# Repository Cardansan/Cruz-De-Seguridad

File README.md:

# Cruz-De-Seguridad
Display Industria 4.0

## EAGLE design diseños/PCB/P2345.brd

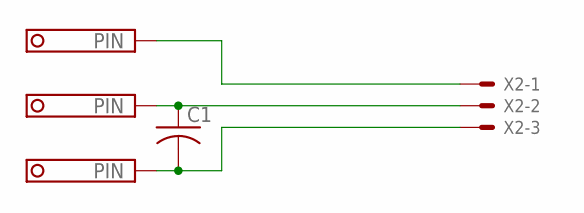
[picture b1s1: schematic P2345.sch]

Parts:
C1: C-US050-024X044; C050-024X044
X1: TERMINAL-BLOCK-3.5MM-3-PIN-ROUND-PAD; TERMINAL-BLOCK-3-PIN-3.5MM-ROUND-PAD
X2: JST-XH-03-PIN-ROUND-PAD; JST-XH-03-PACKAGE-ROUND-PAD

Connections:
unnamed: X1.1, X2.1
unnamed: C1.1, X1.2, X2.2
unnamed: C1.2, X1.3, X2.3

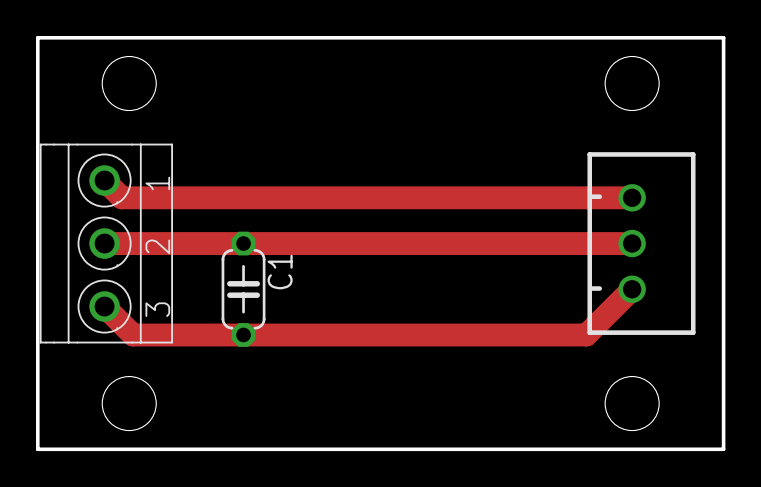
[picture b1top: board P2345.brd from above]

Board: 2 copper layers, 38.1 x 22.9 mm, 3 parts (0 on the bottom side), 3 nets.

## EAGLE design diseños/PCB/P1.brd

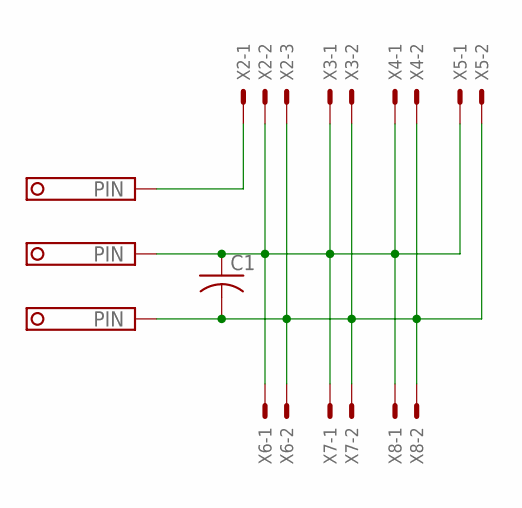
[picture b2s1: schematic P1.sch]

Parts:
C1: C-US050-024X044; C050-024X044
X1: TERMINAL-BLOCK-3.5MM-3-PIN-ROUND-PAD; TERMINAL-BLOCK-3-PIN-3.5MM-ROUND-PAD
X2: JST-XH-03-PIN-ROUND-PAD; JST-XH-03-PACKAGE-ROUND-PAD
X3, X4, X5, X6, X7, X8: JST-XH-02-PIN-ROUND-PAD; JST-XH-02-PACKAGE-ROUND-PAD

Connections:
unnamed: X1.1, X2.1
unnamed: C1.2, X1.3, X2.3, X3.2, X4.2, X5.2, X6.2, X7.2, X8.2
unnamed: C1.1, X1.2, X2.2, X3.1, X4.1, X5.1, X6.1, X7.1, X8.1

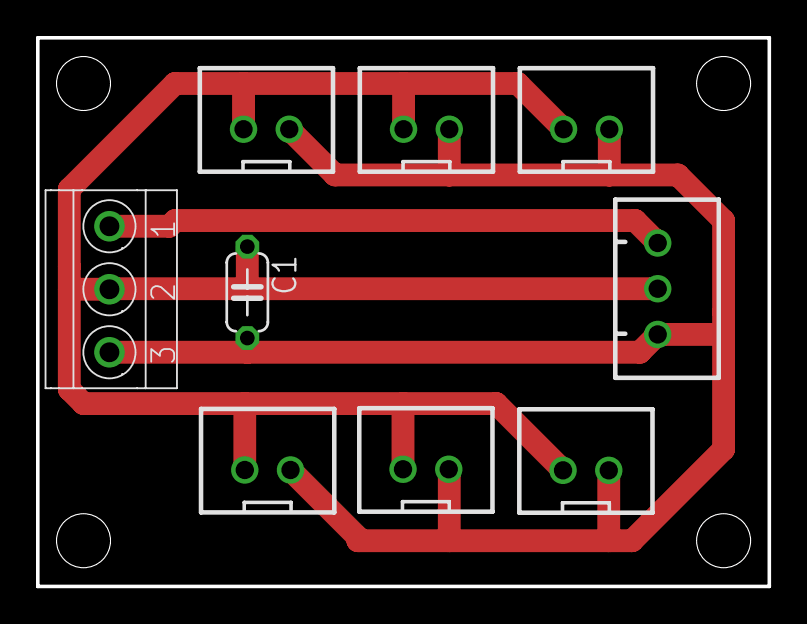
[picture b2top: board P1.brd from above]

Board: 2 copper layers, 40.6 x 30.5 mm, 9 parts (0 on the bottom side), 3 nets.

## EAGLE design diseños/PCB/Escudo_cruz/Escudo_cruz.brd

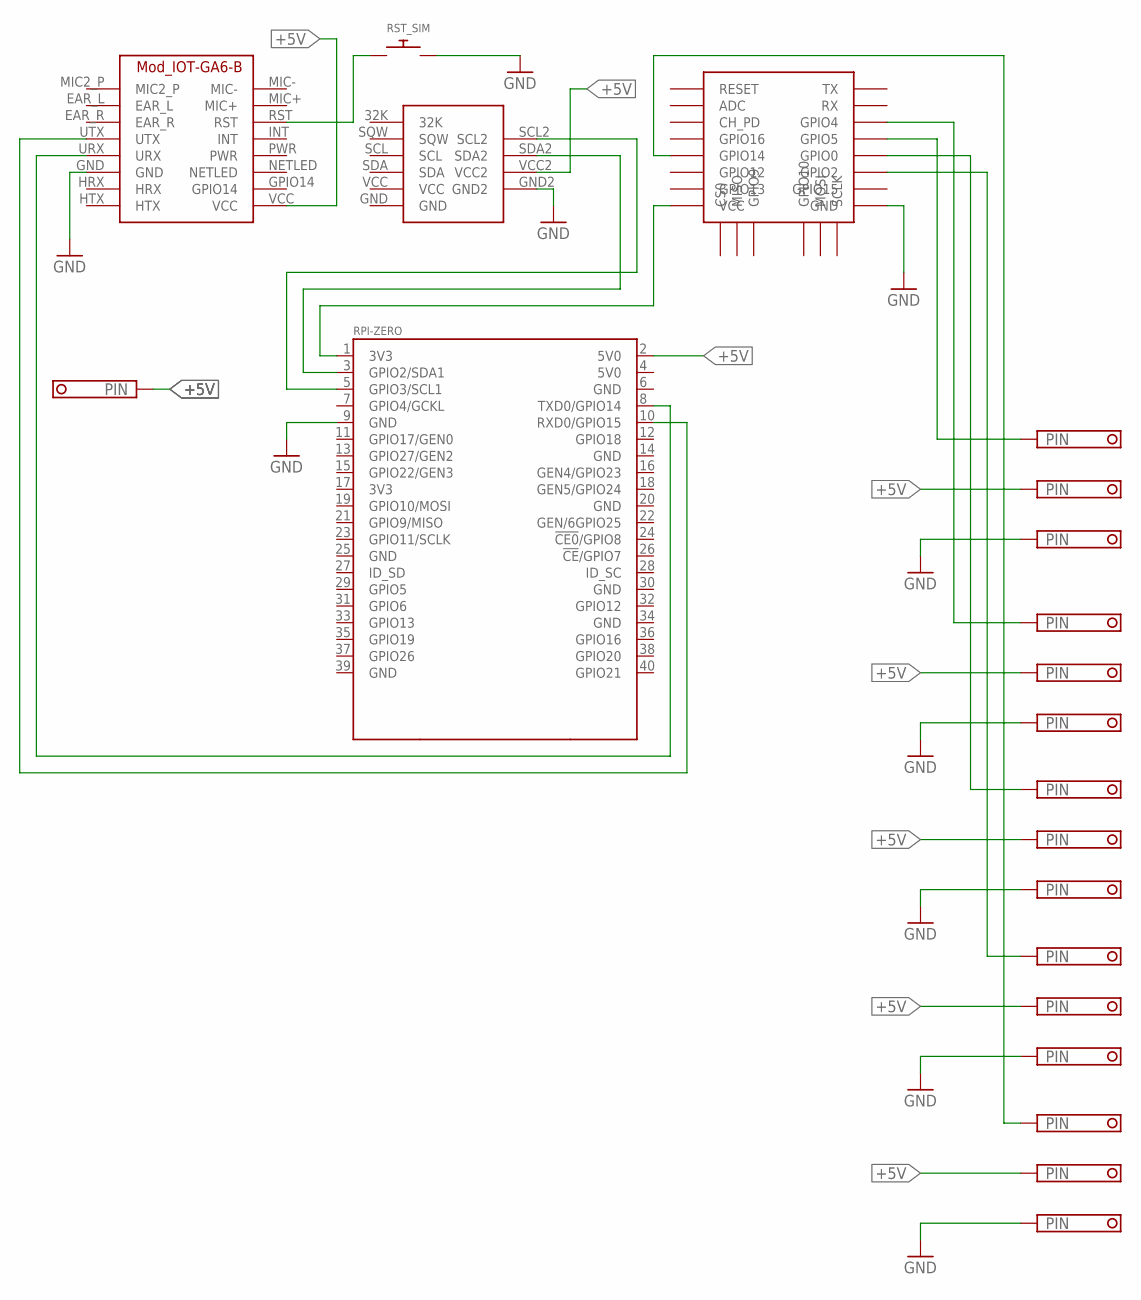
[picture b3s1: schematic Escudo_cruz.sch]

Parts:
AÑO: TERMINAL-BLOCK-3.5MM-3-PIN-ROUND-PAD; TERMINAL-BLOCK-3-PIN-3.5MM-ROUND-PAD
CRUZ: TERMINAL-BLOCK-3.5MM-3-PIN-ROUND-PAD; TERMINAL-BLOCK-3-PIN-3.5MM-ROUND-PAD
DÍAZ: TERMINAL-BLOCK-3.5MM-3-PIN-ROUND-PAD; TERMINAL-BLOCK-3-PIN-3.5MM-ROUND-PAD
ESP8266: ESP12Q
INDICADOR: TERMINAL-BLOCK-3.5MM-3-PIN-ROUND-PAD; TERMINAL-BLOCK-3-PIN-3.5MM-ROUND-PAD
MES: TERMINAL-BLOCK-3.5MM-3-PIN-ROUND-PAD; TERMINAL-BLOCK-3-PIN-3.5MM-ROUND-PAD
POWER: TERMINAL-BLOCK-3.5MM-2-PIN-ROUND-PAD; TERMINAL-BLOCK-2-PIN-3.5MM-ROUND-PAD
RST_SIM: SWITCH_PUSHBUTTONSOFTTOUCHSMD_SJ; PUSHBUTTON_SMD_SJ
SIM: IOT-GA6-B
U$2: RPI-ZERO; RASPBERRYPI_BASTELSTUBE_V13_RASPI_BOARD_B+_FULL
U$4: RTC_DS3231

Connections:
3V3@1: ESP8266.VCC, U$2.1 (3V3)
+5V: AÑO.2, CRUZ.2, DÍAZ.2, MES.2, POWER.1, SIM.VCC, U$2.2 (5V0)
GND: AÑO.3, CRUZ.3, DÍAZ.3, ESP8266.GND, INDICADOR.3, MES.3, RST_SIM.P$2, SIM.GND, U$4.GND2
GND@1: U$2.9 (GND)
unnamed: SIM.URX, U$2.8 (TXD0/GPIO14)
unnamed: SIM.UTX, U$2.10 (RXD0/GPIO15)
unnamed: U$2.3 (GPIO2/SDA1), U$4.SDA2
unnamed: U$2.5 (GPIO3/SCL1), U$4.SCL2
unnamed: RST_SIM.P$1, SIM.RST
unnamed: CRUZ.1, ESP8266.GPIO5
unnamed: ESP8266.GPIO14, INDICADOR.1
unnamed: DÍAZ.1, ESP8266.GPIO4
unnamed: ESP8266.GPIO0, MES.1
unnamed: AÑO.1, ESP8266.GPIO2

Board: 2 copper layers, 11 parts (1 on the bottom side), 13 nets, no tracks yet.

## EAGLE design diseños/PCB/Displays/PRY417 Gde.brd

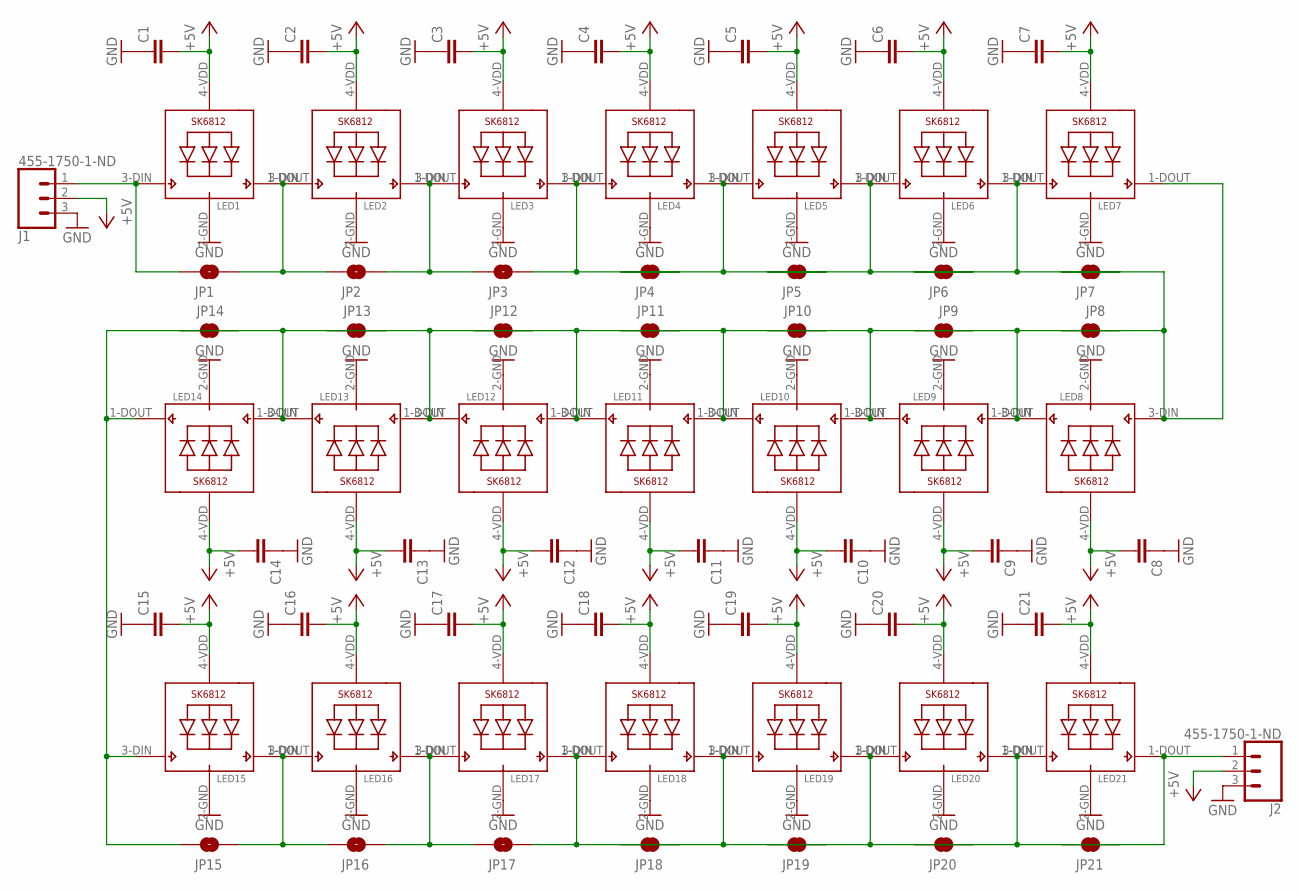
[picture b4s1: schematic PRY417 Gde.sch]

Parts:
C1, C2, C3, C4, C5, C6, C7, C8, C9, C10, C11, C12, C13, C14, C15, C16, C17, C18, C19, C20, C21: C-EUC1206; C1206
J1, J2: 455-1750-1-ND; 1X03
JP1, JP2, JP3, JP4, JP5, JP6, JP7, JP8, JP9, JP10, JP11, JP12, JP13, JP14, JP15, JP16, JP17, JP18, JP19, JP20, JP21: JUMPER-SMT_2_NO_SILK; SMT-JUMPER_2_NO_SILK
LED1, LED2, LED3, LED4, LED5, LED6, LED7, LED8, LED9, LED10, LED11, LED12, LED13, LED14, LED15, LED16, LED17, LED18, LED19, LED20, LED21: SK6812_3535; LED3535

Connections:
+5V: C1.2, C2.2, C3.2, C4.2, C5.2, C6.2, C7.2, C8.2, C9.2, C10.2, C11.2, C12.2, C13.2, C14.2, C15.2, C16.2, C17.2, C18.2, C19.2, C20.2, C21.2, J1.2, J2.2, LED1.4-VDD (VDD), LED2.4-VDD (VDD), LED3.4-VDD (VDD), LED4.4-VDD (VDD), LED5.4-VDD (VDD), LED6.4-VDD (VDD), LED7.4-VDD (VDD), LED8.4-VDD (VDD), LED9.4-VDD (VDD), LED10.4-VDD (VDD), LED11.4-VDD (VDD), LED12.4-VDD (VDD), LED13.4-VDD (VDD), LED14.4-VDD (VDD), LED15.4-VDD (VDD), LED16.4-VDD (VDD), LED17.4-VDD (VDD), LED18.4-VDD (VDD), LED19.4-VDD (VDD), LED20.4-VDD (VDD), LED21.4-VDD (VDD)
GND: C1.1, C2.1, C3.1, C4.1, C5.1, C6.1, C7.1, C8.1, C9.1, C10.1, C11.1, C12.1, C13.1, C14.1, C15.1, C16.1, C17.1, C18.1, C19.1, C20.1, C21.1, J1.3, J2.3, LED1.2-GND (GND), LED2.2-GND (GND), LED3.2-GND (GND), LED4.2-GND (GND), LED5.2-GND (GND), LED6.2-GND (GND), LED7.2-GND (GND), LED8.2-GND (GND), LED9.2-GND (GND), LED10.2-GND (GND), LED11.2-GND (GND), LED12.2-GND (GND), LED13.2-GND (GND), LED14.2-GND (GND), LED15.2-GND (GND), LED16.2-GND (GND), LED17.2-GND (GND), LED18.2-GND (GND), LED19.2-GND (GND), LED20.2-GND (GND), LED21.2-GND (GND)
unnamed: JP1.2, JP2.1, LED1.1-DOUT (DO), LED2.3-DIN (DI)
unnamed: JP2.2, JP3.1, LED2.1-DOUT (DO), LED3.3-DIN (DI)
unnamed: JP3.2, JP4.2, LED3.1-DOUT (DO), LED4.3-DIN (DI)
unnamed: JP4.1, JP5.2, LED4.1-DOUT (DO), LED5.3-DIN (DI)
unnamed: JP5.1, JP6.2, LED5.1-DOUT (DO), LED6.3-DIN (DI)
unnamed: JP6.1, JP7.2, LED6.1-DOUT (DO), LED7.3-DIN (DI)
unnamed: JP8.1, JP9.2, LED8.1-DOUT (DO), LED9.3-DIN (DI)
unnamed: JP9.1, JP10.2, LED9.1-DOUT (DO), LED10.3-DIN (DI)
unnamed: JP10.1, JP11.2, LED10.1-DOUT (DO), LED11.3-DIN (DI)
unnamed: JP11.1, JP12.2, LED11.1-DOUT (DO), LED12.3-DIN (DI)
unnamed: JP12.1, JP13.2, LED12.1-DOUT (DO), LED13.3-DIN (DI)
unnamed: JP13.1, JP14.2, LED13.1-DOUT (DO), LED14.3-DIN (DI)
unnamed: JP7.1, JP8.2, LED7.1-DOUT (DO), LED8.3-DIN (DI)
unnamed: J1.1, JP1.1, LED1.3-DIN (DI)
unnamed: JP14.1, JP15.1, LED14.1-DOUT (DO), LED15.3-DIN (DI)
unnamed: JP15.2, JP16.1, LED15.1-DOUT (DO), LED16.3-DIN (DI)
unnamed: JP16.2, JP17.1, LED16.1-DOUT (DO), LED17.3-DIN (DI)
unnamed: JP17.2, JP18.2, LED17.1-DOUT (DO), LED18.3-DIN (DI)
unnamed: JP18.1, JP19.2, LED18.1-DOUT (DO), LED19.3-DIN (DI)
unnamed: JP19.1, JP20.2, LED19.1-DOUT (DO), LED20.3-DIN (DI)
unnamed: JP20.1, JP21.2, LED20.1-DOUT (DO), LED21.3-DIN (DI)
unnamed: J2.1, JP21.1, LED21.1-DOUT (DO)

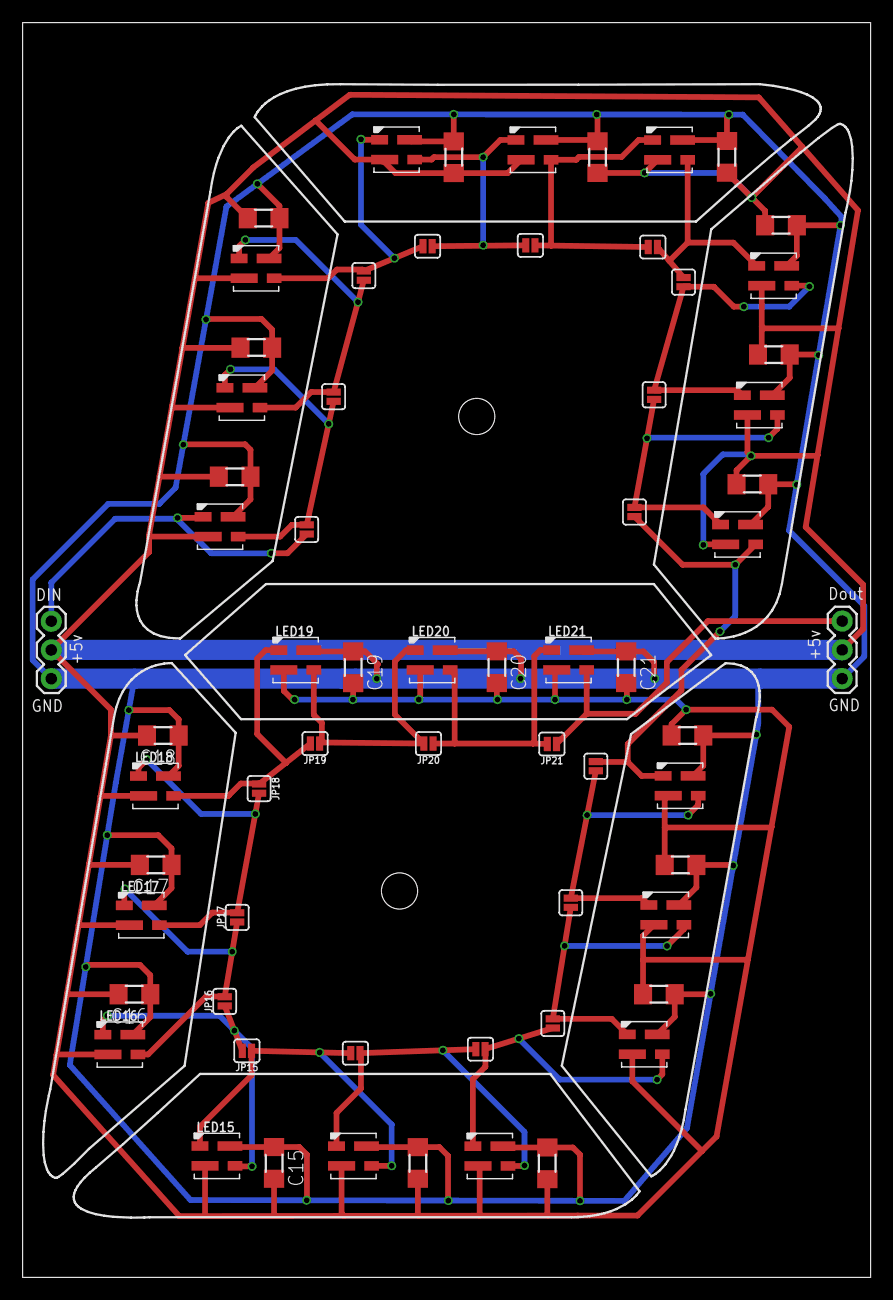
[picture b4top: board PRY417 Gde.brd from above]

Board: 2 copper layers, 74.9 x 110.9 mm, 65 parts (0 on the bottom side), 24 nets.

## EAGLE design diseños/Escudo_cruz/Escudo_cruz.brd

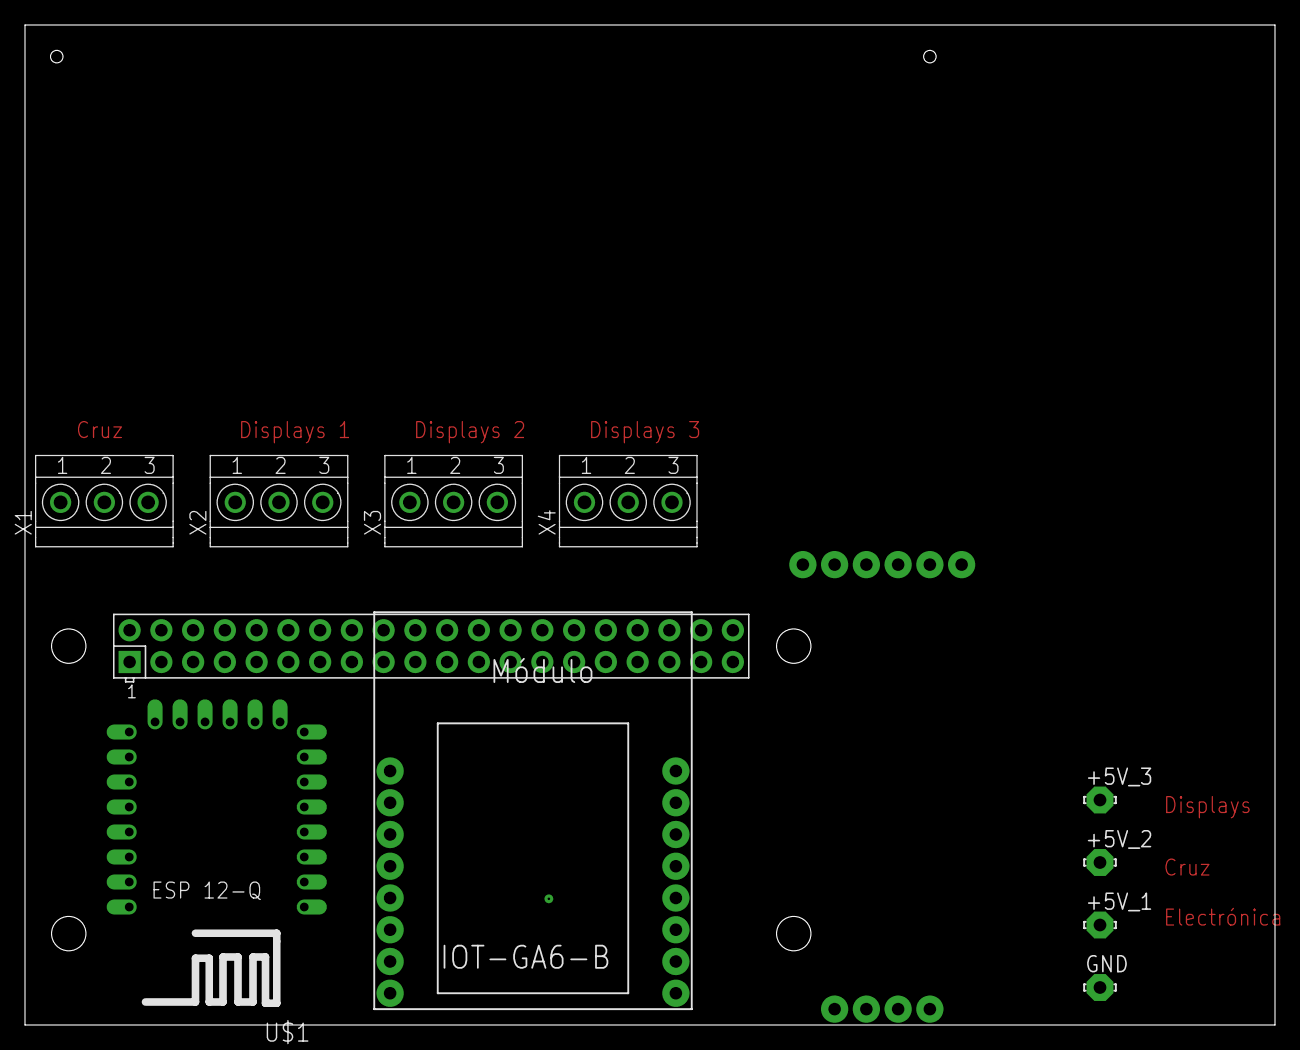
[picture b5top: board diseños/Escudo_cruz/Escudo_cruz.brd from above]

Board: 2 copper layers, 100.0 x 80.0 mm, 12 parts (1 on the bottom side), 12 nets, no tracks yet.

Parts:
+5V_1, +5V_2, +5V_3: LSP10
GND: LSP10
U$1: ESP12Q
U$2: RPI-ZERO; RASPBERRYPI_BASTELSTUBE_V13_RASPI_BOARD_B+_FULL
U$3: IOT-GA6-B
U$4: RTC_DS3231
X1, X2, X3, X4: TERMINAL-BLOCK-3.5MM-3-PIN-ROUND-PAD; TERMINAL-BLOCK-3-PIN-3.5MM-ROUND-PAD

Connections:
+5V_1: +5V_1.MP, U$1.VCC, U$2.2, U$3.VCC, U$4.VCC
+5V_2: +5V_2.MP, X1.2
+5V_3: +5V_3.MP, X2.2, X3.2, X4.2
GND: GND.MP, U$1.GND, U$3.GND, U$4.GND, X1.3, X2.3, X3.3, X4.3
unnamed: U$2.8, U$3.URX
unnamed: U$2.10, U$3.UTX
unnamed: U$1.GPIO12, U$2.3, U$4.SDA
unnamed: U$1.GPIO14, U$2.5, U$4.SCL
unnamed: U$1.GPIO5, X1.1
unnamed: U$1.GPIO4, X2.1
unnamed: U$1.GPIO0, X3.1
unnamed: U$1.GPIO2, X4.1

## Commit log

2019-05-18 Se suben archivos iniciales
2019-05-18 Se sube el primer archivo de flujos.
2019-05-18 Suben diseños de display 4 dígitos
2019-05-18 Reubicacion DXFs
2019-05-18 Create Solidworks Part Document
2019-05-18 Carpeta SolidWorks Parts creada
2019-05-18 Copia de flujos desde tarjeta SD
2019-05-28 Eliminación de duplicados
2019-05-28 Create delete this x2
2019-06-01 Create Modelos
    Delete this x3
2019-06-01 Update Modelos
2019-06-04 Create Delete this x3
2019-06-04 Create Text
2019-06-04 Add files via upload
    PCB con errores corregidos.
    Sólo falta añadir el conector a usar en la entrada*
2019-06-04 Add files via upload
    Suprimir los 3 displays grandes
2019-06-06 Create Ensamble cruz de seguridad
    Los archivos están guardados en .SLDPRT 2018 y como parasolid (.x_t) para que se puedan abrir en Fusion 360 o una versión pasada de Solidworks. Ya hice la prueba de esto.
    Son todos los diseños, 3 niveles por grupo, recordemos que son 3 grupos.
    Para cargar el PCB en el ensamble sugiero abrir PCB.WinRaR ahí vienen todos los componentes del ensamble del PCB. Si no carga por las versiones, importar el CAD PCB.STEP que viene dentro del RaR y ag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
    Agregué el tablero de la cruz gigante junto con su parasolid.
    Y desde luego el ensamble, guardé el mismo ensamble en formatos distintos: como archivo ensamble 2018 (.SLDASM), binario (.x_t) y
2019-06-06 Create H
2019-06-06 Add files via upload
    Adjunto los archivos del ensamble de la cruz. Guardé todos en formato solid 2018 (.SLDPRT), así como en parasolid (.x_t) para que lo puedan abrir en versiones pasadas de solidworks y en fusion.
    Son:
    3 grupos con sus respectivas 3 capas.
    Cruz original el cual es el tablero principal.
    PCB, éste tiene el detalle que es un ensamble complejo, sus componentes están en PCB.rar si no llegara a cargar en el ensamble, también lo guardé en .STEP para abrirlo en cualquier software de diseño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
    Descargué el CAD del tornillo a utilizar, es un M3 x.5x20 obteni
2019-06-17 Placas separadas
2019-06-21 Create :v
2019-06-21 Add files via upload
    DxFs correctos, los que dicen barrenos o cortes son los que se mandarán a cortar
2019-07-26 Extraer flujos antiguos
2019-08-12 Manda dia y color a cruz
2019-08-13 Salida a strip dias totales
2019-08-13 Muestra dias totales
2019-08-13 Seleccion de dia total, mes, año
2019-08-13 Correccion color naranja
2019-08-15 diagrama cruz de seguridad
2019-08-15 se modificó funcion displayAccidente y tuvo errores al mostrar dias en cruz
2019-08-15 Se eliminaron comentarios y lineas no necesarios
2019-08-15 Revert "Se eliminaron comentarios y lineas no necesarios"
    This reverts commit 025126d4075a6d2b00cee23bf482e248f3ba2f30.
2019-08-15 Se quitaron comentarios y se realizaron pruebas en cruz y mes por monitor serial
2019-08-16 Tornillos de cabeza avellanada con hueco hexagonal
    Tornillos para las placas PRY397 y ensamble total de la cruz
2019-08-16 Seleccion de fecha, dias totales, mes, año y seleccion de color. Arduino se desconecta cada cierto tiempo
2019-08-16 Correccion color amarillo, se veìa naranja
2019-08-16 se elimino flow duplicado
2019-08-17 Cambio en mostrar color blanco
2019-08-17 cambio valores color azul
2019-08-17 cambios en interfaz
2019-08-17 Modificaciones de la capa cruz y cruz original
2019-08-19 Cambio de pines de salida para ESP8266 y modificacion de archivo .ini
2019-08-19 mainESP8266.cpp
2019-08-19 Se agregò codigo Wemos a Cruz de seguridad
2019-08-19 Se combina codigo cruz de seguridad con mainESP8266
2019-08-20 Creacion de funcion para obtener IP
2019-08-20 Se regresa a pines anteriores de ESP8266
2019-08-21 Se agrego diseño de shild para raspberry
2019-08-21 Fotofrafias_Cruz-seguridad
    Procedimiento para el montaje
2019-08-21 cambio nombre carpeta
2019-08-21 Fotografias_Cruz-seguridad
    Procedimiento para el montaje
2019-08-22 Fotos tarjeta perforada
2019-08-22 Revisión de unión de programa de página web + puente
    Se movieron las funciones de setup y loop al final del código. Se comentó la parte que transmite del puerto serie a la página web porque aún tiene conflictos, también hay un problema cuando se cambia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
2019-08-23 Correcciones de color e ingreso de la información
    Se resolvió la inicialización más limpia de los datos, los colores son más estables y más definidos, se restringe los datos de fechas y tipo de accidente fuera de rango
2019-08-24 Interfaz de AP con websoket funcionando
    Se separó la página web del resto de código, enviandola a un archivo index.html en una carpeta data, se almacena por SPIFFS, los archivos para spiffs se actualizan en el ESP con el comando en termina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
2019-08-28 Diagrama de conexión
    Shield y Displays de la cruz de seguridad
2019-08-29 Se agregan archivos de ensamble
    archivos utilizados para el ensamble de cruz de seguridad
2019-08-29 Se agregan tuercas a tornillos
2019-08-29 Se agregan capas de cruz, tapas
2019-08-30 Se añaden orificios a la fuente de 5V para su ensamble y caja
2019-08-30 Se agrega ESP para comunicarse mediante I2C con Raspberry
2019-08-30 Correcciones de dimensiones
2019-08-30 actualizacion en ensamble (se agrega caja y fuente de 5v)
2019-09-02 correccion en dimensiones de ensamble
2019-09-02 Se añaden orificios para pines en capas displays dias totales, mes y año
2019-09-02 DXF de capas para mes y año
2019-09-03 Se añaden PCB a capa de mes y año, y se movió posición de la fuente de 5v en caja
2019-09-04 Internet SIM+Raspberry
    Archivos de configuracion para hacer coneccion ppp
2019-09-04 Cambios
    Cortes de las capas 1-3 del grupo 2 y capas1 y 3 del grupo 3. Ademas de modificar la capa original para el grupo 2.
2019-09-06 Se agregaron restricciones a los comandos serie
    En días sin accidentes se agregó la restricción entre 0 y 9999, y en mes de 1 a 12
2019-09-06 Corrección en display de días
    Se cambiaron nomenclaturas para reorganizar el orden de los LEDs y Displays en función de colocar las unidades al inicio de la tira e ir creciendo según los leds por segmento y la cantidad de dígitos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
2019-09-06 Reorganización de display días y año
    Se arregló el orden de los display en función de seguir la lógica de empezar por unidades y hacer la trayectoria de los leds en S, se cambión en la función para enviar el blanco directamente ya que e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
2019-09-07 Correccion Display MES
    Se hizo una funcion especial pjunto con su arreglo para resolver que el display se encuentra invertido y la entrada está en las decenas, se resolvió que los números no se pasen de sus límites lógicos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
2019-09-07 Orden y reordenamiento de los flujos,
2019-09-09 Cortes Mes y Año
    Grupo tres capa 1 y 3
2019-09-09 Se ordenaron los flujos
2019-09-10 Se agregó el protocolo I2C
    Para sustituir la comunicación por puerto serie en los módulos
2019-09-10 Se agregó OTA por WEB
    Ahora se puede actualizar el archivo binario del código inalambricamente al accecer a la ip, http://192.168.4.1/update
2019-09-10 Se actualizó OTA para el firmware y la pagina WEB
    Ahora se pueden enviar también archivos estando en la red wifi con el siguiente método por la terminal
    curl -F "file=@$PWD/index.html" 192.168.4.1/web
    y con eso se actualiza el archivo de la pagina web tambien por OTA
2019-09-11 Se eliminó I2C, se ajustaron colores por nivel de accidente
    El ESP no funciona normalmente como esclavo de i2c, para hacerlo funcionar es necesario modificar varias librerias.
    Se ajusto para que el color de los display de días, mes y año coincidieran con el color según el nivel de accidente, debido a que estos se mostraran segun el nivel de accidente del día actual.
    Se cambio "," por ")" para la comunicación serie
2019-09-11 Modificaciones SHIELD raspberry
    Se descarta la idea de la comunicación I2C y se agrega una quinta salida de display para indicar la tonalidad del tipo de accidente.
    Cambios a los cortes del grupo 2 capas 1, 2 y 3
2019-09-12 Se reconfiguraron las ventanas del dashboard, se utiliza la librería de 'moment' en las funciones de los nodos
2019-09-12 Ajuste de letras para comando serie
    Se cambiaron los comandos por puerto serie porque se generan comandos basura que los estaba activando quedando ahora
    n - para ingresar fecha en la cruz
    t - total de días sin accidente
    m - mes actual
    y - año actual
    c - limpiar cruz
2019-09-12 Se ajustaron los comandos por puerto serie para evitar reacciones por letras basura
    n - para ingresar fecha en la cruz
    t - total de días sin accidente
    m - mes actual
    y - año actual
    c - limpiar cruz
2019-09-13 Se envían ya los días sin accidente con un contero automático, aún se debe corregir el cambio de hora y fecha para sistema y tambien hacer que funcione la hora de cambio, ya se dibuja el mes y año
2019-09-13 Manda un arreglo con los días y el nivel de accidente al panel
2019-09-14 Se actualiza la fecha desde el panel principal y se guarda en global
2019-09-14 Se agregó la función de cambiar el color de los días, el mes y el año en función del nivel de accidente del día actual
2019-09-16 El accidente incapacitante puede reiniciar la cuenta en automàtico cuando se modifica en ajustes, reinicia la cuenta si es el día actual, o la actualiza según la cantidad de días
2019-09-16 Se modificó un poco la interfaz, se cambió de orden, aún no se resuelve el cambio de hora desde el hardware, al parecer el cambio no es permanente, pero se mantiene probablemnte de internet
2019-09-20 Ya funciona ajuste de hora
2019-10-02 se descomentó el APN para selecionar Telcel
2019-10-04 Placas adicionales para la cruz digital
    Placas P1 Y P2345 alimentación para los displays.
2019-11-02 Bump node-red-dashboard from 2.16.2 to 2.17.1
    Bumps [node-red-dashboard](https://github.com/node-red/node-red-dashboard) from 2.16.2 to 2.17.1.
    - [Release notes](https://github.com/node-red/node-red-dashboard/releases)
    - [Changelog](https://github.com/node-red/node-red-dashboard/blob/master/CHANGELOG.md)
    - [Commits](https://github.com/node-red/node-red-dashboard/compare/2.16.2...2.17.1)

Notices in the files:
parts and their libraries:
SparkFun-Jumpers: Licensing: Creative Commons ShareAlike 4.0 International - https://creativecommons.org/licenses/by-sa/4.0
